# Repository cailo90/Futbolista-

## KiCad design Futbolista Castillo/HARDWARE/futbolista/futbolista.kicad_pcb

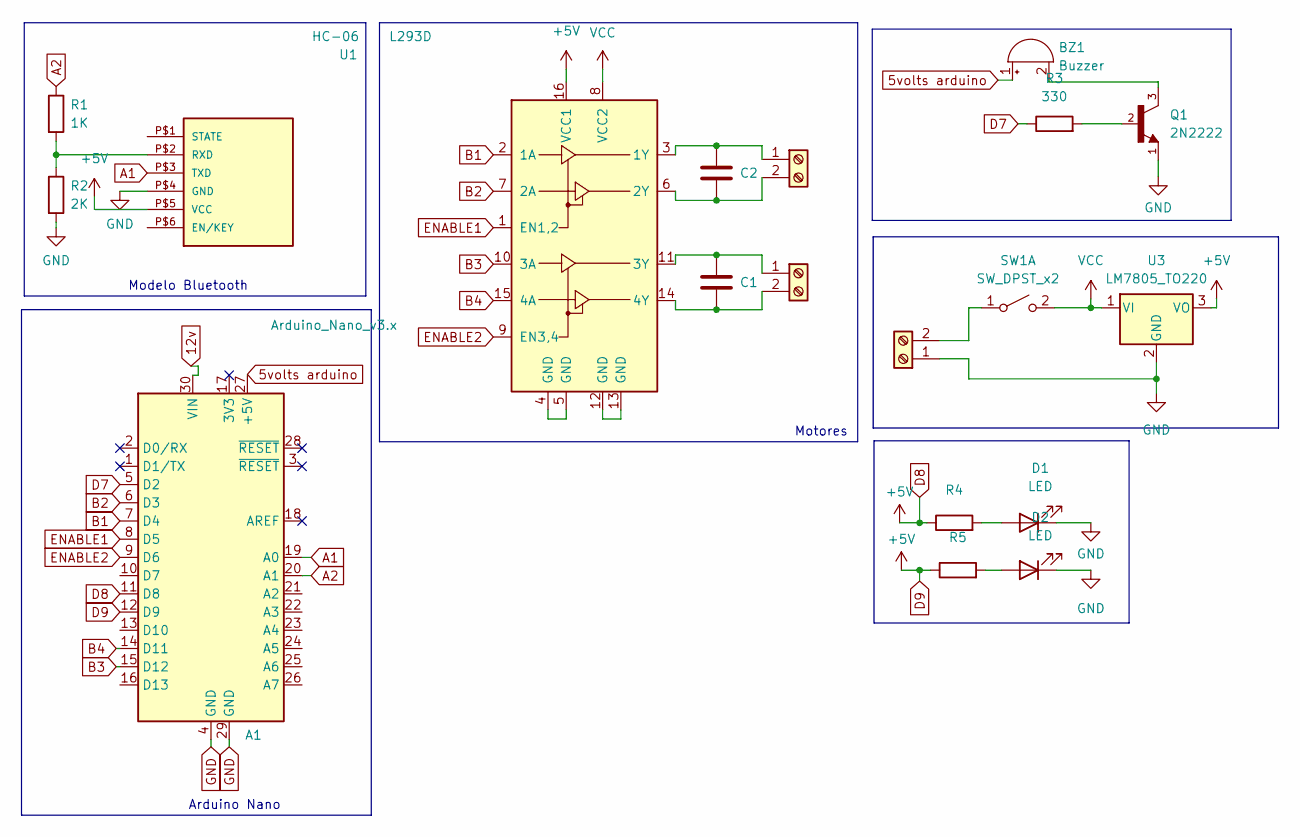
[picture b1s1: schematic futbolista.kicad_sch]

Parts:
A1: Arduino_Nano_v3.x; Arduino_Nano
BZ1: Buzzer; Buzzer_12mm
C1, C2: C; C_Disc_D4.3mm_W1.9mm_P5.00mm
D1, D2: LED; LED_D3.0mm
J1, J2, J3: Screw_Terminal_01x02; TerminalBlock_Altech_AK300-2_P5.00mm
Q1: 2N2222; TO127P584H533-3; PARTREV R2
R1: 1K; R_Axial_DIN0204_L3.6mm_D1.6mm_P5.08mm_Horizontal
R2: 2K; R_Axial_DIN0204_L3.6mm_D1.6mm_P5.08mm_Horizontal
R3: 330; R_Axial_DIN0204_L3.6mm_D1.6mm_P5.08mm_Horizontal
R4, R5: R_Axial_DIN0204_L3.6mm_D1.6mm_P5.08mm_Horizontal
SW1: SW_DPST_x2; SW_100SP1T1B4M2QE
U1: HC-06
U2: L293D; DIP-16_W7.62mm
U3: LM7805_TO220; TO-220-3_Vertical

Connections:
5volts arduino: A1.27 (+5V), BZ1.1 (+)
12v: A1.30 (VIN)
A1: A1.19 (A0), U1.P$3 (TXD)
A2: A1.20 (A1), R1.1
B1: A1.7 (D4), U2.2 (1A)
B2: A1.6 (D3), U2.7 (2A)
B3: A1.15 (D12), U2.10 (3A)
B4: A1.14 (D11), U2.15 (4A)
D7: A1.5 (D2), R3.1
D8: A1.11 (D8), A1.12 (D9), R4.1, R5.1, U1.P$5 (VCC), U2.16 (VCC1), U3.3 (VO)
ENABLE1: A1.8 (D5), U2.1 (EN1,2)
ENABLE2: A1.9 (D6), U2.9 (EN3,4)
GND: A1.4 (GND), A1.29 (GND), D1.1 (K), D2.1 (K), J3.1, Q1.1, R2.2, U1.P$4 (GND), U3.2 (GND)
unnamed: BZ1.2 (-), Q1.3
unnamed: D1.2 (A), R4.2
unnamed: D2.2 (A), R5.2
unnamed: C1.1, J1.1, U2.11 (3Y)
unnamed: C1.2, J1.2, U2.14 (4Y)
unnamed: C2.1, J2.1, U2.3 (1Y)
unnamed: C2.2, J2.2, U2.6 (2Y)
unnamed: J3.2, SW1.1 (A)
unnamed: Q1.2, R3.2
unnamed: R1.2, R2.1, U1.P$2 (RXD)
unnamed: U2.4 (GND), U2.5 (GND)
unnamed: U2.12 (GND), U2.13 (GND)
VCC: SW1.2 (B), U2.8 (VCC2), U3.1 (VI)

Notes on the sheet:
Motores
Arduino Nano
Modelo Bluetooth

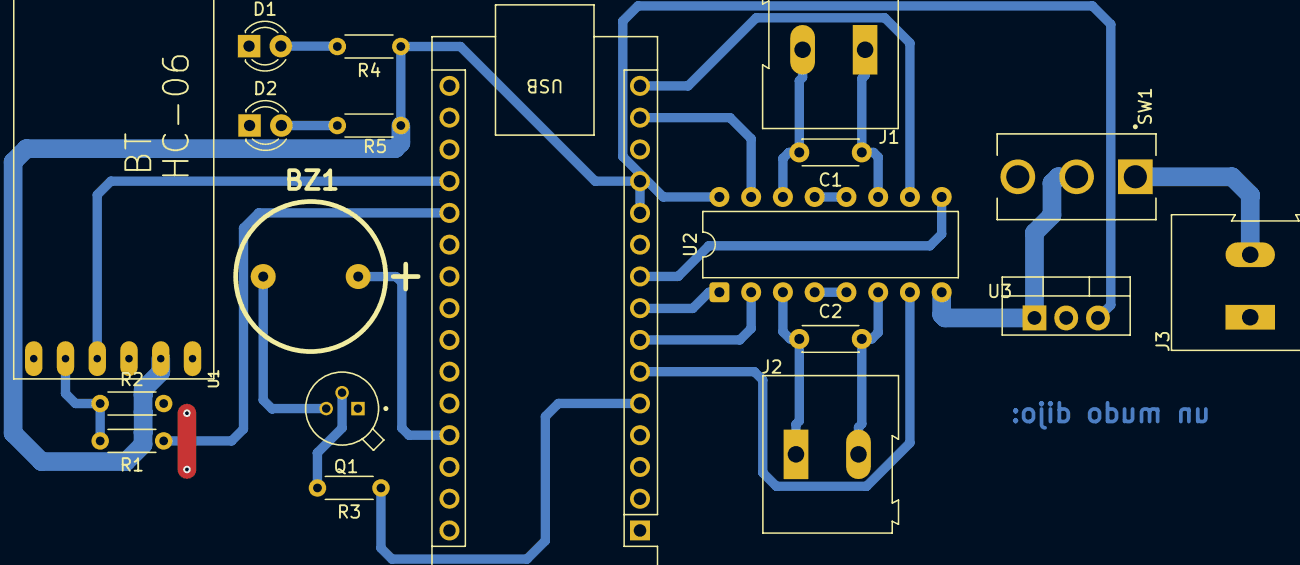
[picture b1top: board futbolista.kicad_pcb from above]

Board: 2 copper layers, 19 parts (0 on the bottom side), 25 nets.
